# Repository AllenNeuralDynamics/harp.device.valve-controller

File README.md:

A Harp-compliant, 16-channel MOSFET Output board for valve control.

## Features
* Up to 5A total current consumption
* Up to 2A on any single output channel
* 8-GPIO expansion header

## Enclosure
See the companion [Onshape project](https://cad.onshape.com/documents/b68e9ca81d13baa37ddbb87a/w/239401edd39de6ea07d882fc/e/2e7e06ce5de5ab57a801ffd8) for the PCBA enclosure.

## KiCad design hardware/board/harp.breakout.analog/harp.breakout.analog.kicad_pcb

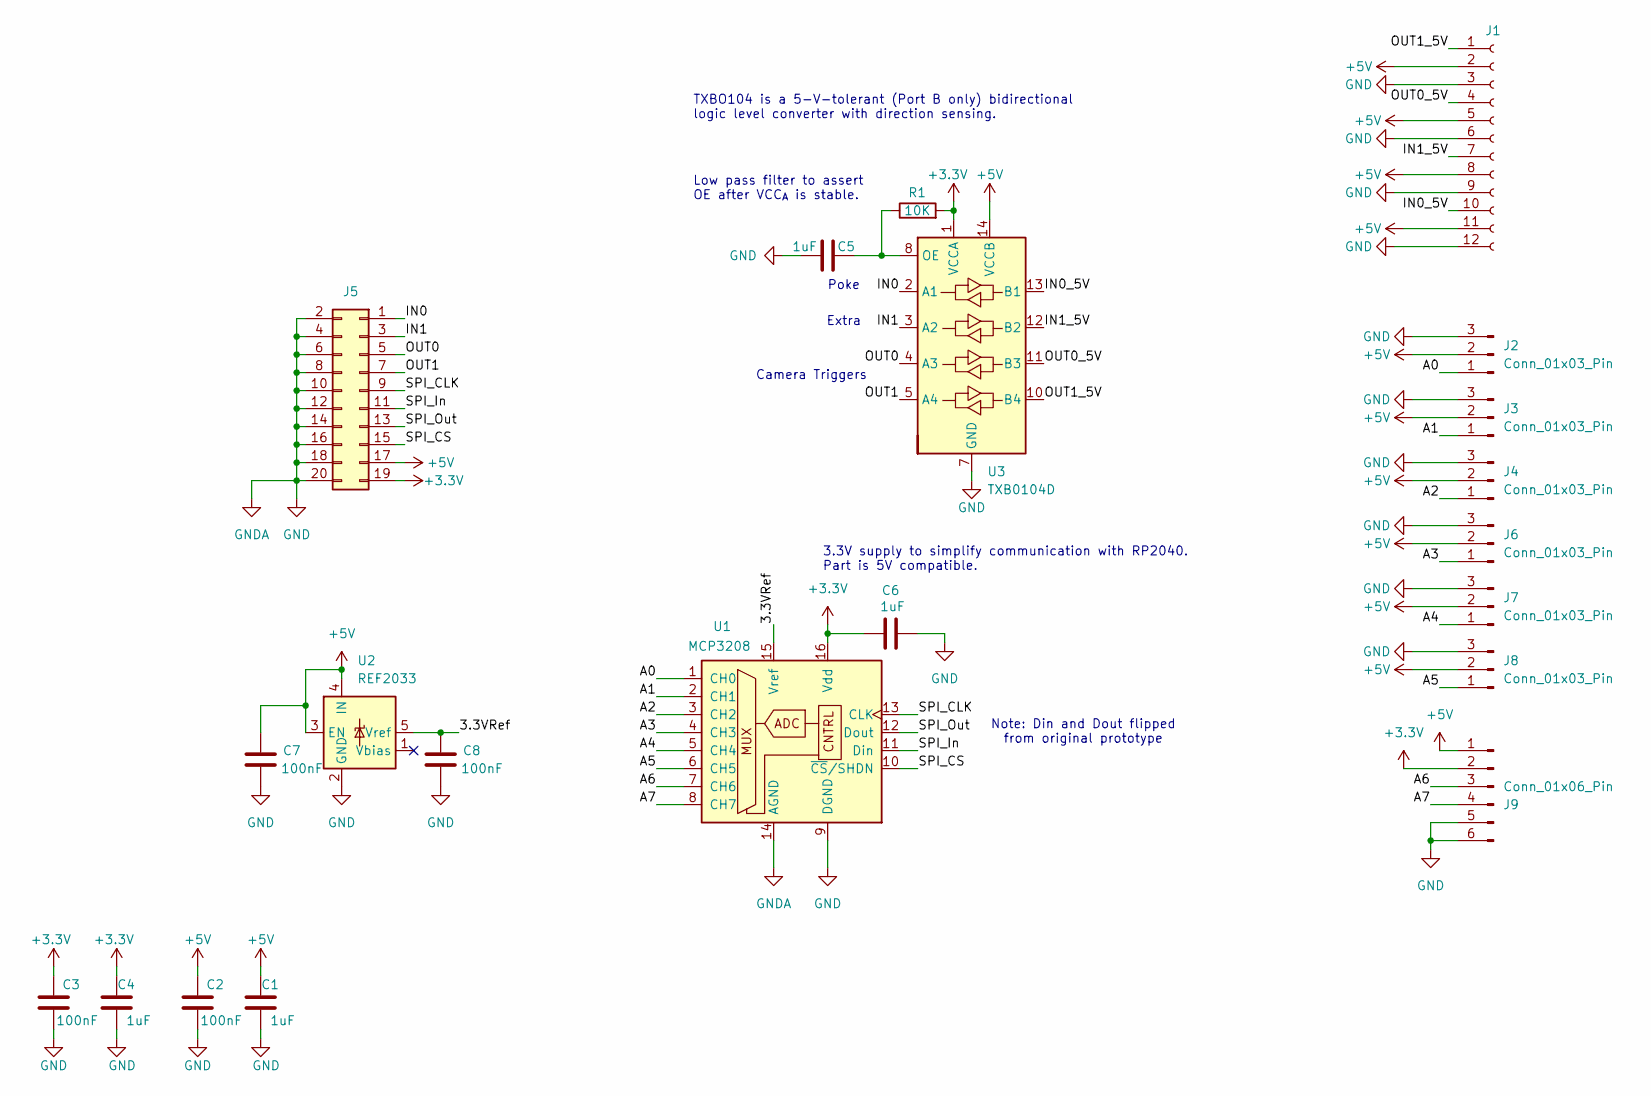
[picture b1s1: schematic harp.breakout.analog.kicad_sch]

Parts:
C1, C4, C5: 1uF; C_0402_1005Metric_Pad0.74x0.62mm_HandSolder; Rated Voltage 35V
C2, C3: 100nF; C_0402_1005Metric_Pad0.74x0.62mm_HandSolder; Rated Voltage 50V; Tolerance 10%
C6: 1uF; C_0402_1005Metric_Pad0.74x0.62mm_HandSolder
C7, C8: 100nF; C_0402_1005Metric_Pad0.74x0.62mm_HandSolder
J1: Conn_01x12_Socket; 3M_Mini-Clamp-Socket-37212-62M3-003PL-3x4_Vertical
J2, J3, J4, J6, J7, J8: Conn_01x03_Pin; CONN_705530002_03_MOL
J5: Conn_02x10_Odd_Even; PinSocket_2x10_P2.54mm_Vertical
J9: Conn_01x06_Pin; PinHeader_1x06_P2.54mm_Vertical
R1: 10K; R_0402_1005Metric_Pad0.72x0.64mm_HandSolder
U1: MCP3208; DIP-16_W7.62mm_LongPads
U2: REF2033; SOT-23-5
U3: TXB0104D; SOIC-14_3.9x8.7mm_P1.27mm

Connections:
+3.3V: C3.2, C4.1, C6.1, J5.19, J9.2, R1.2, U1.16 (Vdd), U3.1 (VCCA)
+5V: C1.1, C2.2, C7.1, J1.2, J1.5, J1.8, J1.11, J2.2, J3.2, J4.2, J5.17, J6.2, J7.2, J8.2, J9.1, U2.3 (EN), U2.4 (IN), U3.14 (VCCB)
/3.3VRef: C8.1, U1.15 (Vref), U2.5 (Vref)
/A0: J2.1, U1.1 (CH0)
/A1: J3.1, U1.2 (CH1)
/A2: J4.1, U1.3 (CH2)
/A3: J6.1, U1.4 (CH3)
/A4: J7.1, U1.5 (CH4)
/A5: J8.1, U1.6 (CH5)
/A6: J9.3, U1.7 (CH6)
/A7: J9.4, U1.8 (CH7)
/IN0: J5.1, U3.2 (A1)
/IN0_5V: J1.10, U3.13 (B1)
/IN1: J5.3, U3.3 (A2)
/IN1_5V: J1.7, U3.12 (B2)
/OUT0: J5.5, U3.4 (A3)
/OUT0_5V: J1.4, U3.11 (B3)
/OUT1: J5.7, U3.5 (A4)
/OUT1_5V: J1.1, U3.10 (B4)
/SPI_CLK: J5.9, U1.13 (CLK)
/SPI_CS: J5.15, U1.10 (~CS/SHDN)
/SPI_In: J5.11, U1.11 (Din)
/SPI_Out: J5.13, U1.12 (Dout)
GND: C1.2, C2.1, C3.1, C4.2, C5.2, C6.2, C7.2, C8.2, J1.3, J1.6, J1.9, J1.12, J2.3, J3.3, J4.3, J5.2, J5.4, J5.6, J5.8, J5.10, J5.12, J5.14, J5.16, J5.18, J5.20, J6.3, J7.3, J8.3, J9.5, J9.6, U1.9 (DGND), U1.14 (AGND), U2.2 (GND), U3.7 (GND)
unnamed: C5.1, R1.1, U3.8 (OE)

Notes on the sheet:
3.3V supply to simplify communication with RP2040. Part is 5V compatible.
Camera Triggers
Low pass filter to assert OE after VCC_{A} is stable.
Poke
TXBO104 is a 5-V-tolerant (Port B only) bidirectional logic level converter with direction sensing.
Note: Din and Dout flipped from original prototype
Extra

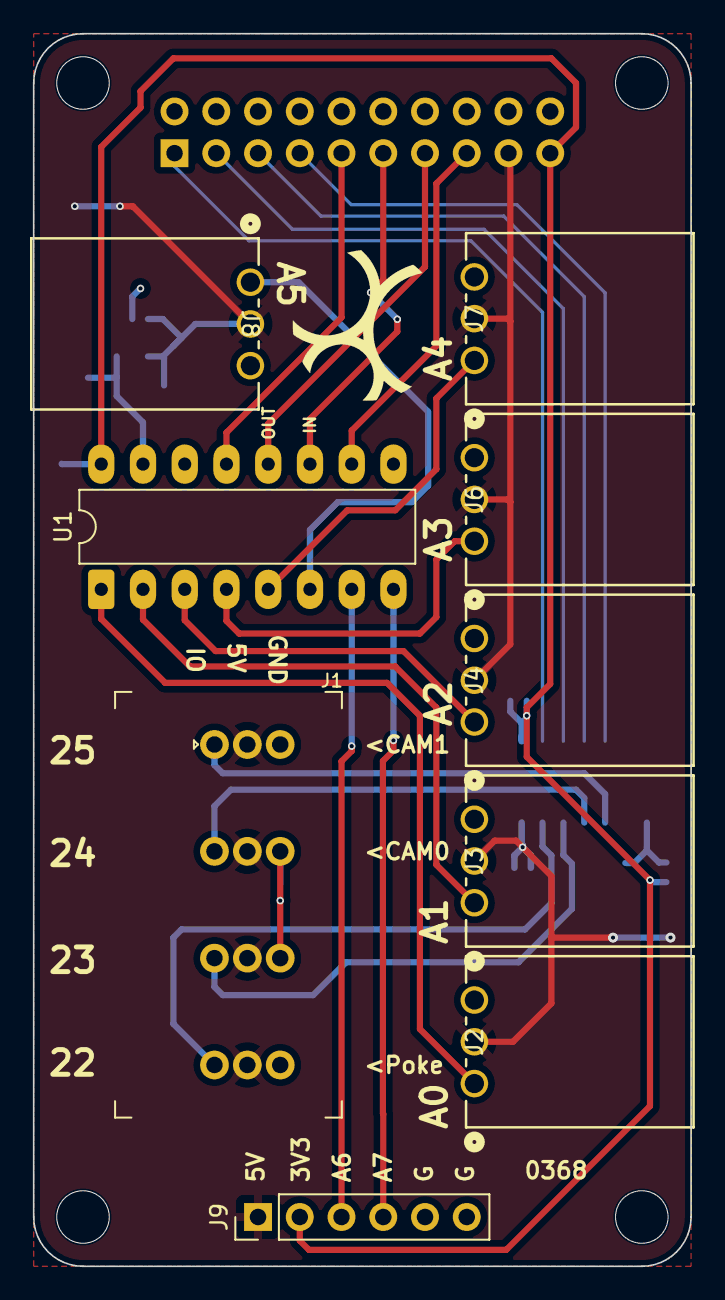
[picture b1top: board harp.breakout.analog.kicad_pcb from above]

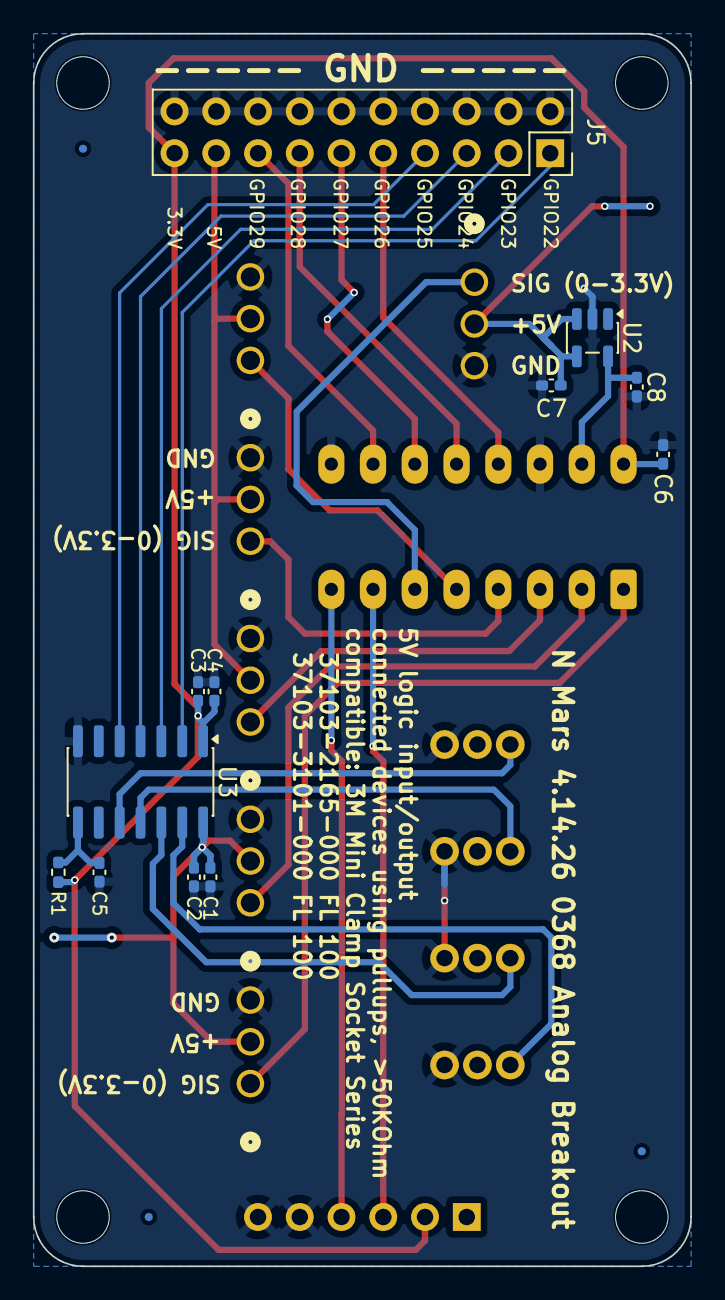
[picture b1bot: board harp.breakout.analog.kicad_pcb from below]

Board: 2 copper layers, 40.0 x 75.0 mm, 24 parts (15 on the bottom side), 25 nets.

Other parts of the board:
FID2, FID2#2, FID2#3: Fiducial; Fiducial_0.5mm_Mask1mm

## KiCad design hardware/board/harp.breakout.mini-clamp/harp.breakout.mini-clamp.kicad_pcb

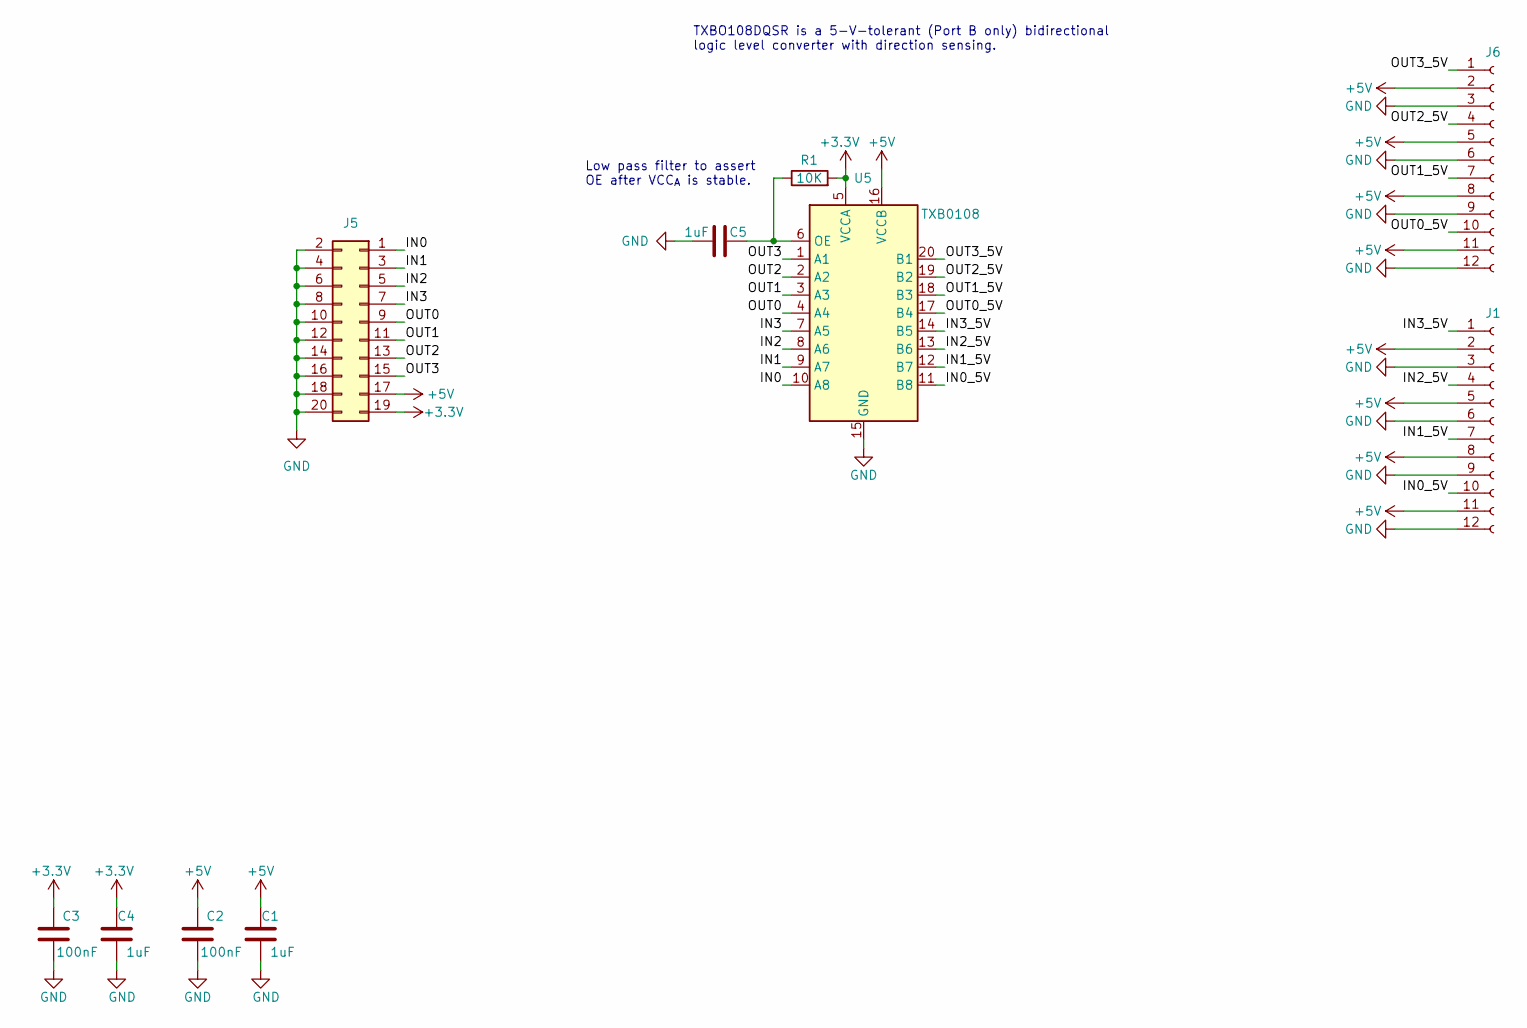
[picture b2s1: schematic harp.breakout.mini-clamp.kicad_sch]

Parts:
C1, C4, C5: 1uF; C_0402_1005Metric_Pad0.74x0.62mm_HandSolder; Rated Voltage 35V
C2, C3: 100nF; C_0402_1005Metric_Pad0.74x0.62mm_HandSolder; Rated Voltage 50V; Tolerance 10%
J1, J6: Conn_01x12_Socket; 3M_Mini-Clamp-Socket-37212-62M3-003PL-3x4_Vertical
J5: Conn_02x10_Odd_Even; PinSocket_2x10_P2.54mm_Vertical
R1: 10K; R_0402_1005Metric_Pad0.72x0.64mm_HandSolder
U5: TXB0108; TSSOP-20_4.4x6.5mm_P0.65mm

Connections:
+3.3V: C3.2, C4.1, J5.19, R1.2, U5.5 (VCCA)
+5V: C1.1, C2.2, J1.2, J1.5, J1.8, J1.11, J5.17, J6.2, J6.5, J6.8, J6.11, U5.16 (VCCB)
/IN0: J5.1, U5.10 (A8)
/IN0_5V: J1.10, U5.11 (B8)
/IN1: J5.3, U5.9 (A7)
/IN1_5V: J1.7, U5.12 (B7)
/IN2: J5.5, U5.8 (A6)
/IN2_5V: J1.4, U5.13 (B6)
/IN3: J5.7, U5.7 (A5)
/IN3_5V: J1.1, U5.14 (B5)
/OUT0: J5.9, U5.4 (A4)
/OUT0_5V: J6.10, U5.17 (B4)
/OUT1: J5.11, U5.3 (A3)
/OUT1_5V: J6.7, U5.18 (B3)
/OUT2: J5.13, U5.2 (A2)
/OUT2_5V: J6.4, U5.19 (B2)
/OUT3: J5.15, U5.1 (A1)
/OUT3_5V: J6.1, U5.20 (B1)
GND: C1.2, C2.1, C3.1, C4.2, C5.2, J1.3, J1.6, J1.9, J1.12, J5.2, J5.4, J5.6, J5.8, J5.10, J5.12, J5.14, J5.16, J5.18, J5.20, J6.3, J6.6, J6.9, J6.12, U5.15 (GND)
unnamed: C5.1, R1.1, U5.6 (OE)

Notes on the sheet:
Low pass filter to assert OE after VCC_{A} is stable.
TXBO108DQSR is a 5-V-tolerant (Port B only) bidirectional logic level converter with direction sensing.

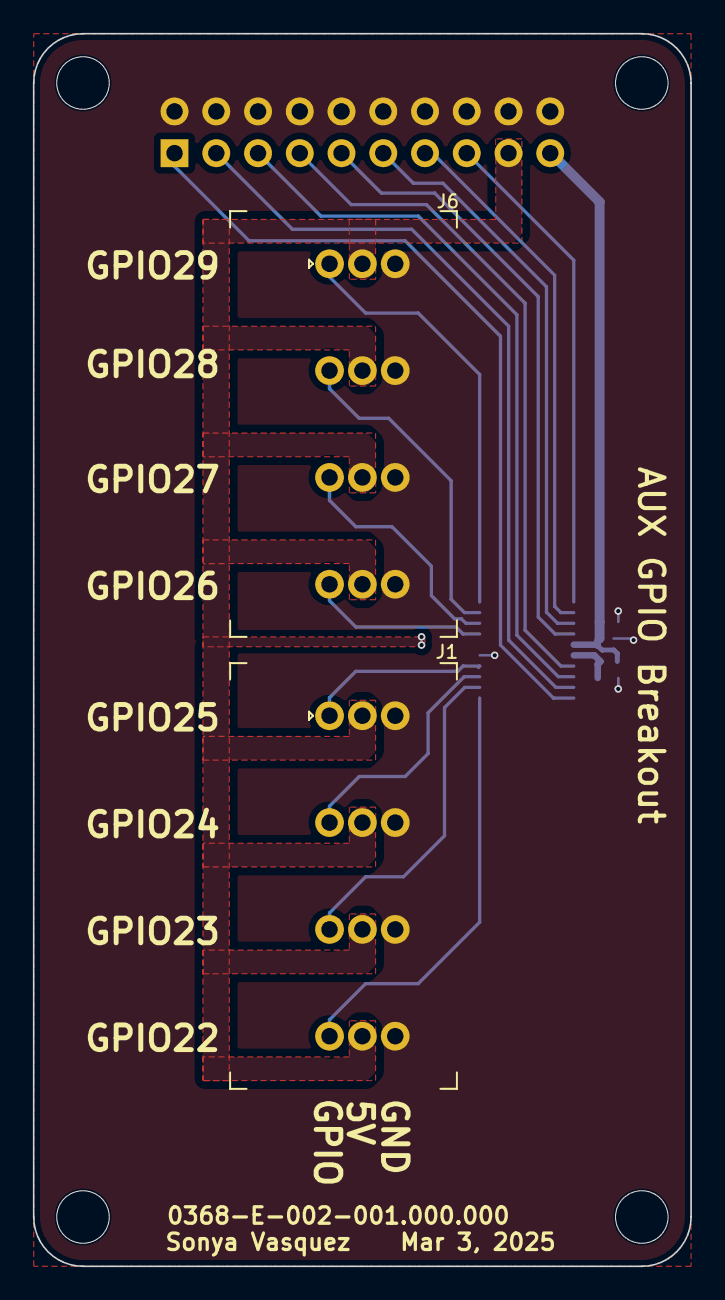
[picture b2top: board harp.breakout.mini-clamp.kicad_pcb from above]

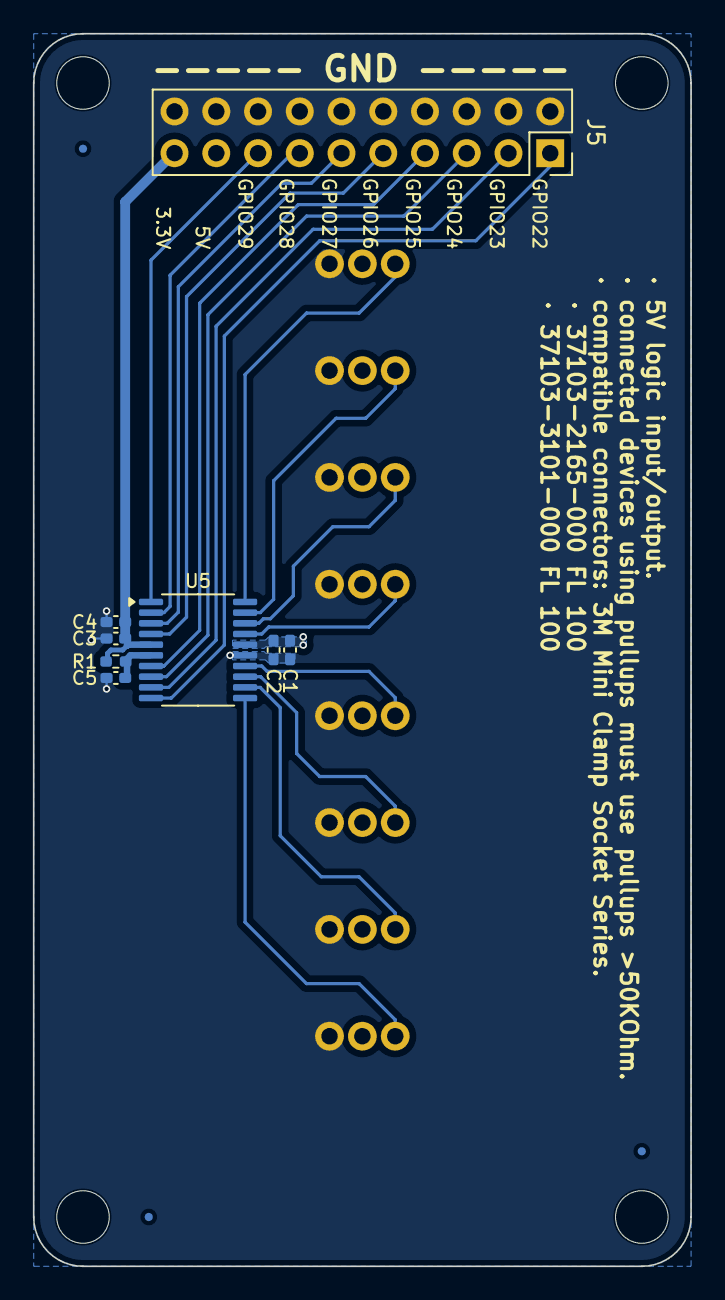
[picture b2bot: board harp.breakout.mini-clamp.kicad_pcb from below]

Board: 2 copper layers, 40.0 x 75.0 mm, 13 parts (11 on the bottom side), 20 nets.

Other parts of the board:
FID2, FID2#2, FID2#3: Fiducial; Fiducial_0.5mm_Mask1mm

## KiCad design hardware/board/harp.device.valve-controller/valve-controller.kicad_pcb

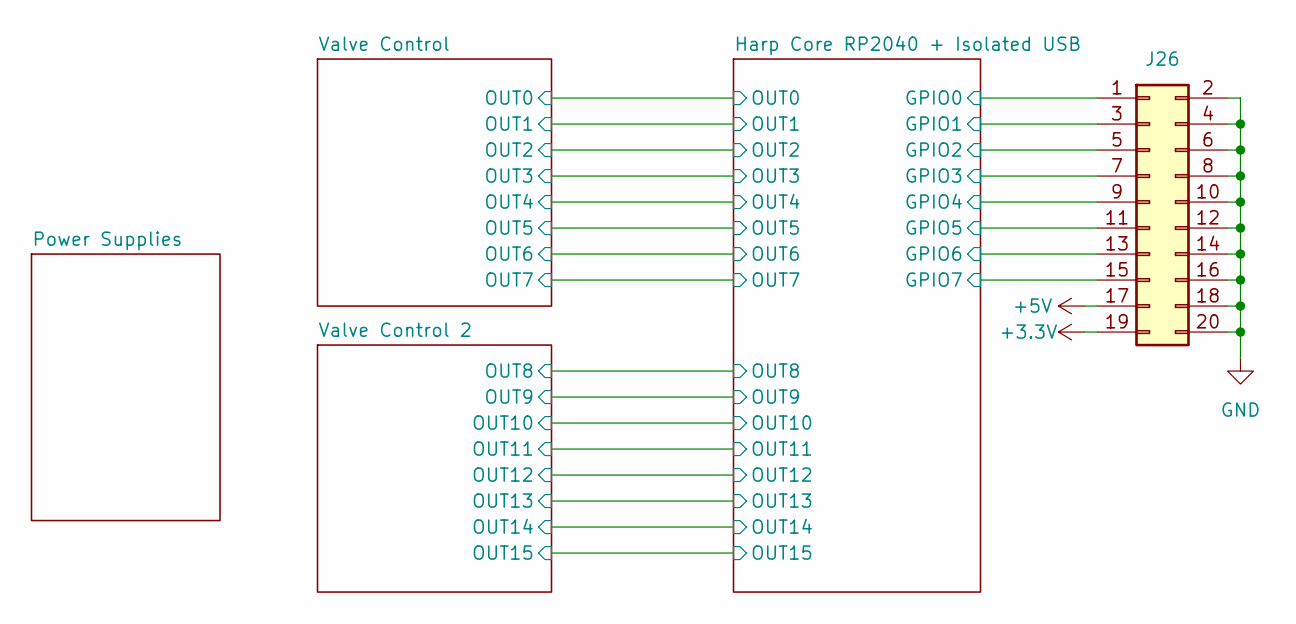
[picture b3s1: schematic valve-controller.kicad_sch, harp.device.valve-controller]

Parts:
J26: Conn_02x10_Odd_Even; PinHeader_2x10_P2.54mm_Vertical_SMD

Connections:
+3.3V: J26.19; also elsewhere on the board
+5V: J26.17; also elsewhere on the board
/Harp Core RP2040 + Isolated USB/GPIO0: J26.1; also elsewhere on the board
/Harp Core RP2040 + Isolated USB/GPIO1: J26.3; also elsewhere on the board
/Harp Core RP2040 + Isolated USB/GPIO2: J26.5; also elsewhere on the board
/Harp Core RP2040 + Isolated USB/GPIO3: J26.7; also elsewhere on the board
/Harp Core RP2040 + Isolated USB/GPIO4: J26.9; also elsewhere on the board
/Harp Core RP2040 + Isolated USB/GPIO5: J26.11; also elsewhere on the board
/Harp Core RP2040 + Isolated USB/GPIO6: J26.13; also elsewhere on the board
/Harp Core RP2040 + Isolated USB/GPIO7: J26.15; also elsewhere on the board
GND: J26.2, J26.4, J26.6, J26.8, J26.10, J26.12, J26.14, J26.16, J26.18, J26.20; also elsewhere on the board

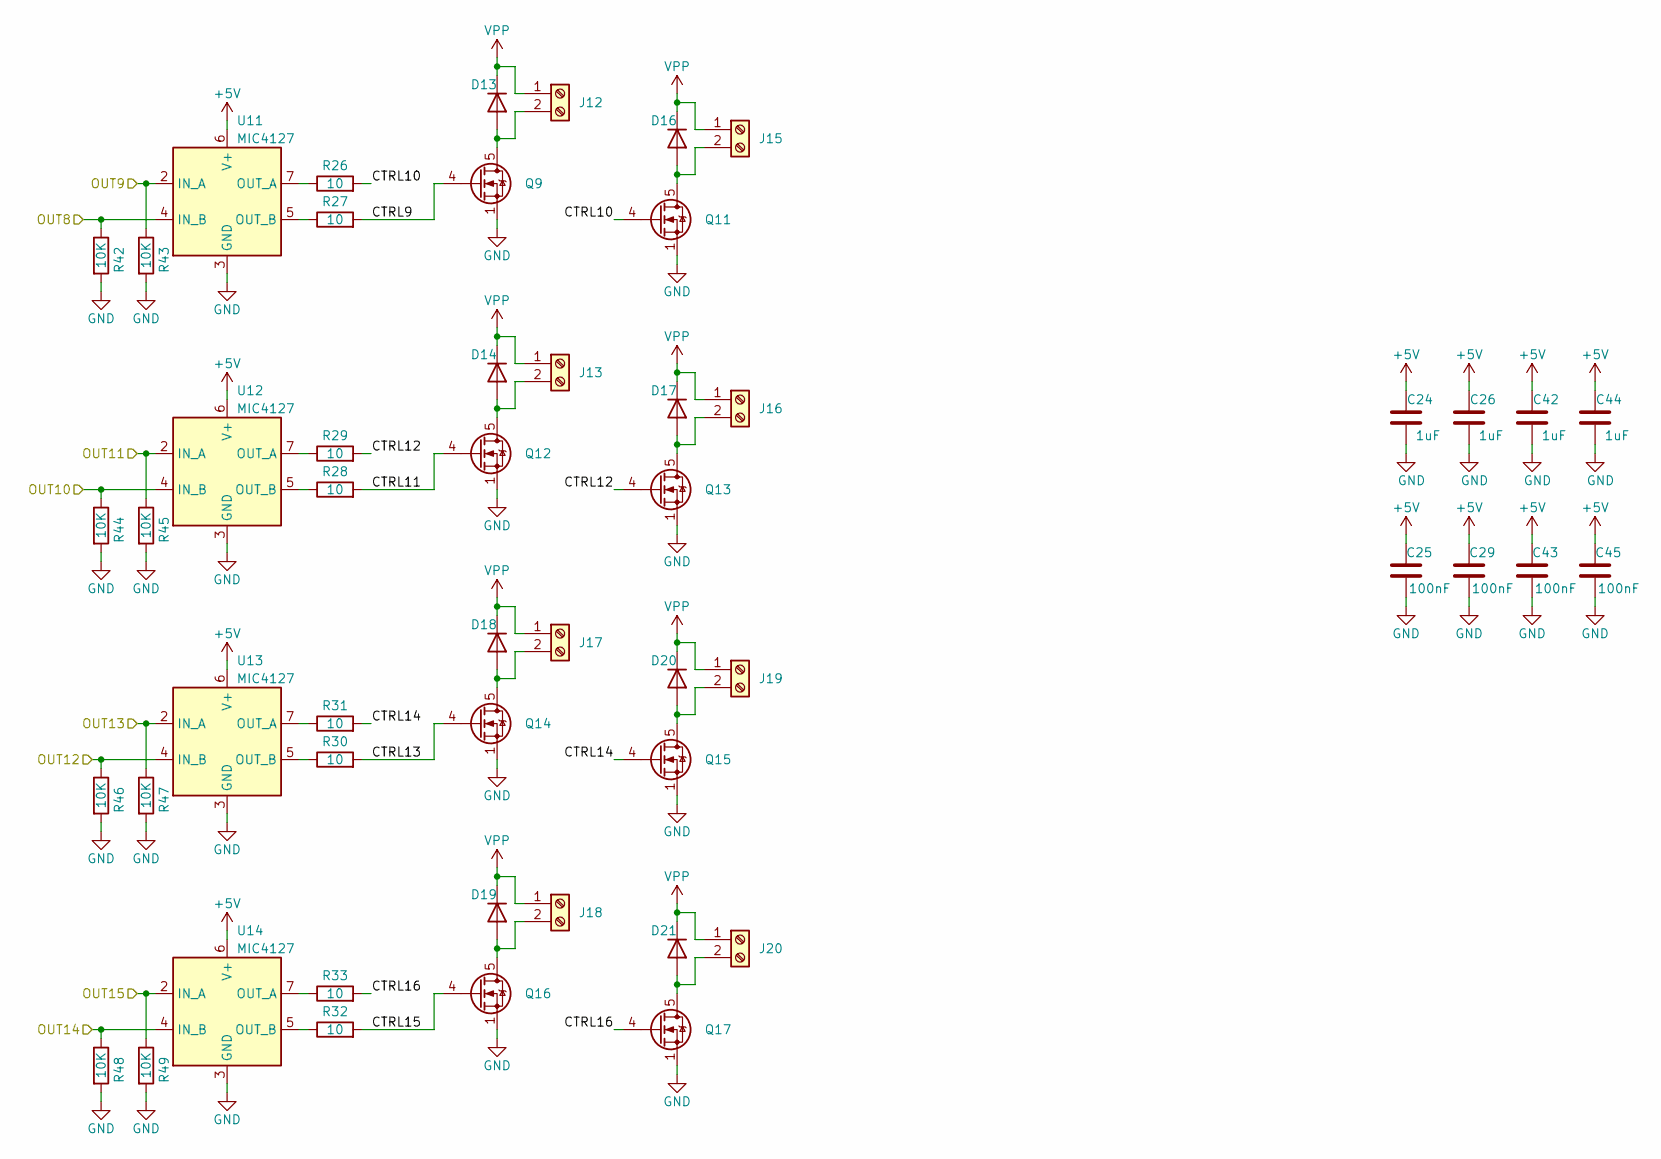
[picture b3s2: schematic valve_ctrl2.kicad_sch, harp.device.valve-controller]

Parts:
C24, C26, C42, C44: 1uF; C_0402_1005Metric; Rated Voltage 35V
C25, C29, C43, C45: 100nF; C_0402_1005Metric; Rated Voltage 50V; Tolerance 10%
D13, D14, D16, D17, D18, D19, D20, D21: 1N4007FL; D_SOD-123F
J12, J13, J15, J16, J17, J18, J19, J20: Screw_Terminal_01x02; PhoenixContact_MC_1,5_2-G-3.5_1x02_P3.50mm_Horizontal
Q9, Q11, Q12, Q13, Q14, Q15, Q16, Q17: CSD17570Q5B; TDSON-8-1
R26, R27, R28, R29, R30, R31, R32, R33: 10; R_0603_1608Metric; Tolerance 1%
R42, R43, R44, R45, R46, R47, R48, R49: 10K; R_0402_1005Metric
U11, U12, U13, U14: MIC4127; MSOP-8-1EP_3x3mm_P0.65mm_EP1.5x1.8mm

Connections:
+5V: C24.1, C25.2, C26.1, C29.2, C42.1, C43.2, C44.1, C45.2, U11.6 (V+), U12.6 (V+), U13.6 (V+), U14.6 (V+); also elsewhere on the board
/Harp Core RP2040 + Isolated USB/OUT8: R42.1, U11.4 (IN_B); also elsewhere on the board
/Harp Core RP2040 + Isolated USB/OUT9: R43.1, U11.2 (IN_A); also elsewhere on the board
/Harp Core RP2040 + Isolated USB/OUT10: R44.1, U12.4 (IN_B); also elsewhere on the board
/Harp Core RP2040 + Isolated USB/OUT11: R45.1, U12.2 (IN_A); also elsewhere on the board
/Harp Core RP2040 + Isolated USB/OUT12: R46.1, U13.4 (IN_B); also elsewhere on the board
/Harp Core RP2040 + Isolated USB/OUT13: R47.1, U13.2 (IN_A); also elsewhere on the board
/Harp Core RP2040 + Isolated USB/OUT14: R48.1, U14.4 (IN_B); also elsewhere on the board
/Harp Core RP2040 + Isolated USB/OUT15: R49.1, U14.2 (IN_A); also elsewhere on the board
/Valve Control 2/CTRL9: Q9.4 (G), R27.2
/Valve Control 2/CTRL10: Q11.4 (G), R26.2
/Valve Control 2/CTRL11: Q12.4 (G), R28.2
/Valve Control 2/CTRL12: Q13.4 (G), R29.2
/Valve Control 2/CTRL13: Q14.4 (G), R30.2
/Valve Control 2/CTRL14: Q15.4 (G), R31.2
/Valve Control 2/CTRL15: Q16.4 (G), R32.2
/Valve Control 2/CTRL16: Q17.4 (G), R33.2
GND: C24.2, C25.1, C26.2, C29.1, C42.2, C43.1, C44.2, C45.1, Q9.1 (S), Q9.2 (S), Q9.3 (S), Q11.1 (S), Q11.2 (S), Q11.3 (S), Q12.1 (S), Q12.2 (S), Q12.3 (S), Q13.1 (S), Q13.2 (S), Q13.3 (S), Q14.1 (S), Q14.2 (S), Q14.3 (S), Q15.1 (S), Q15.2 (S), Q15.3 (S), Q16.1 (S), Q16.2 (S), Q16.3 (S), Q17.1 (S), Q17.2 (S), Q17.3 (S), R42.2, R43.2, R44.2, R45.2, R46.2, R47.2, R48.2, R49.2, U11.3 (GND), U11.9 (GND), U12.3 (GND), U12.9 (GND), U13.3 (GND), U13.9 (GND), U14.3 (GND), U14.9 (GND); also elsewhere on the board
unnamed: D13.2 (A), J12.2, Q9.5 (D)
unnamed: D14.2 (A), J13.2, Q12.5 (D)
unnamed: D16.2 (A), J15.2, Q11.5 (D)
unnamed: D17.2 (A), J16.2, Q13.5 (D)
unnamed: D18.2 (A), J17.2, Q14.5 (D)
unnamed: D19.2 (A), J18.2, Q16.5 (D)
unnamed: D20.2 (A), J19.2, Q15.5 (D)
unnamed: D21.2 (A), J20.2, Q17.5 (D)
unnamed: R26.1, U11.7 (OUT_A)
unnamed: R27.1, U11.5 (OUT_B)
unnamed: R29.1, U12.7 (OUT_A)
unnamed: R28.1, U12.5 (OUT_B)
unnamed: R31.1, U13.7 (OUT_A)
unnamed: R30.1, U13.5 (OUT_B)
unnamed: R33.1, U14.7 (OUT_A)
unnamed: R32.1, U14.5 (OUT_B)
VPP: D13.1 (K), D14.1 (K), D16.1 (K), D17.1 (K), D18.1 (K), D19.1 (K), D20.1 (K), D21.1 (K), J12.1, J13.1, J15.1, J16.1, J17.1, J18.1, J19.1, J20.1; also elsewhere on the board

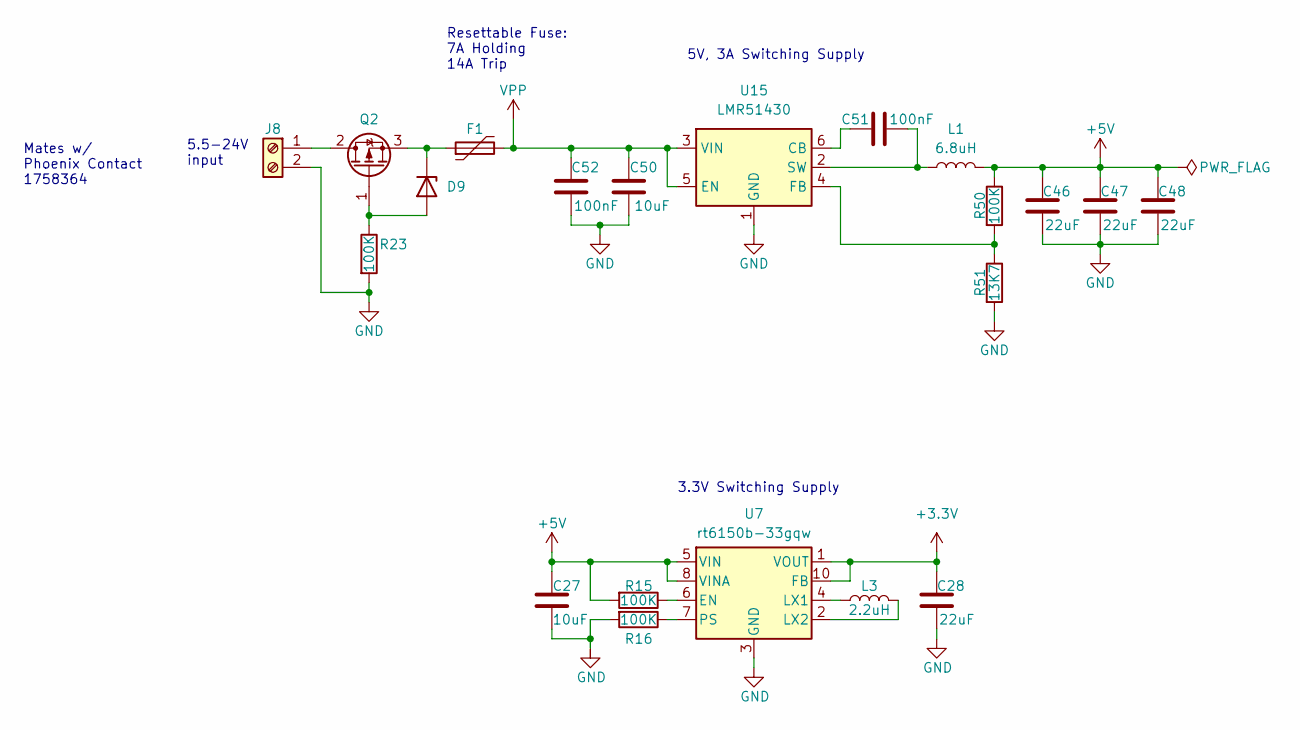
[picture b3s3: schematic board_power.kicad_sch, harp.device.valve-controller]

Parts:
C27, C50: 10uF; C_0805_2012Metric
C28, C46, C47, C48: 22uF; C_0805_2012Metric; Rated Voltage 10V
C51, C52: 100nF; C_0402_1005Metric; Rated Voltage 50V; Tolerance 10%
D9: BZV55B15; D_MiniMELF
F1: Polyfuse; Fuse_2920_7451Metric
J8: Screw_Terminal_01x02; PhoenixContact_MSTBA_2,5_2-G-5,08_1x02_P5.08mm_Horizontal
L1: 6.8uH; L_Bourns_SRR1260
L3: 2.2uH; L_0603_1608Metric
Q2: GSFD4005; TO-252-2
R15, R16, R23, R50: 100K; R_0402_1005Metric; Tolerance 1%
R51: 13K7; R_0402_1005Metric; Tolerance 1%
U7: rt6150b-33gqw; WDFN-10-1EP_2.5x2.5mm_P0.5_EP1.25x2.1mm
U15: LMR51430; SOT-23-6

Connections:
+3.3V: C28.2, U7.1 (VOUT), U7.10 (FB); also elsewhere on the board
+5V: C27.1, C46.2, C47.2, C48.2, L1.2, R15.2, R50.1, U7.5 (VIN), U7.8 (VINA); also elsewhere on the board
GND: C27.2, C28.1, C46.1, C47.1, C48.1, C50.2, C52.1, J8.2, R16.2, R23.2, R51.2, U7.3 (GND), U7.9 (GND), U7.11 (GND), U15.1 (GND); also elsewhere on the board
unnamed: D9.2 (A), Q2.1 (G), R23.1
unnamed: D9.1 (K), F1.1, Q2.3 (S)
unnamed: J8.1, Q2.2 (D)
unnamed: R15.1, U7.6 (EN)
unnamed: L3.1, U7.4 (LX1)
unnamed: L3.2, U7.2 (LX2)
unnamed: R16.1, U7.7 (PS)
unnamed: C51.2, U15.6 (CB)
unnamed: R50.2, R51.1, U15.4 (FB)
unnamed: C51.1, L1.1, U15.2 (SW)
VPP: C50.1, C52.2, F1.2, U15.3 (VIN), U15.5 (EN); also elsewhere on the board

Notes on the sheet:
5.5-24V input
3.3V Switching Supply
Mates w/ Phoenix Contact 1758364
5V, 3A Switching Supply
Resettable Fuse: 7A Holding 14A Trip

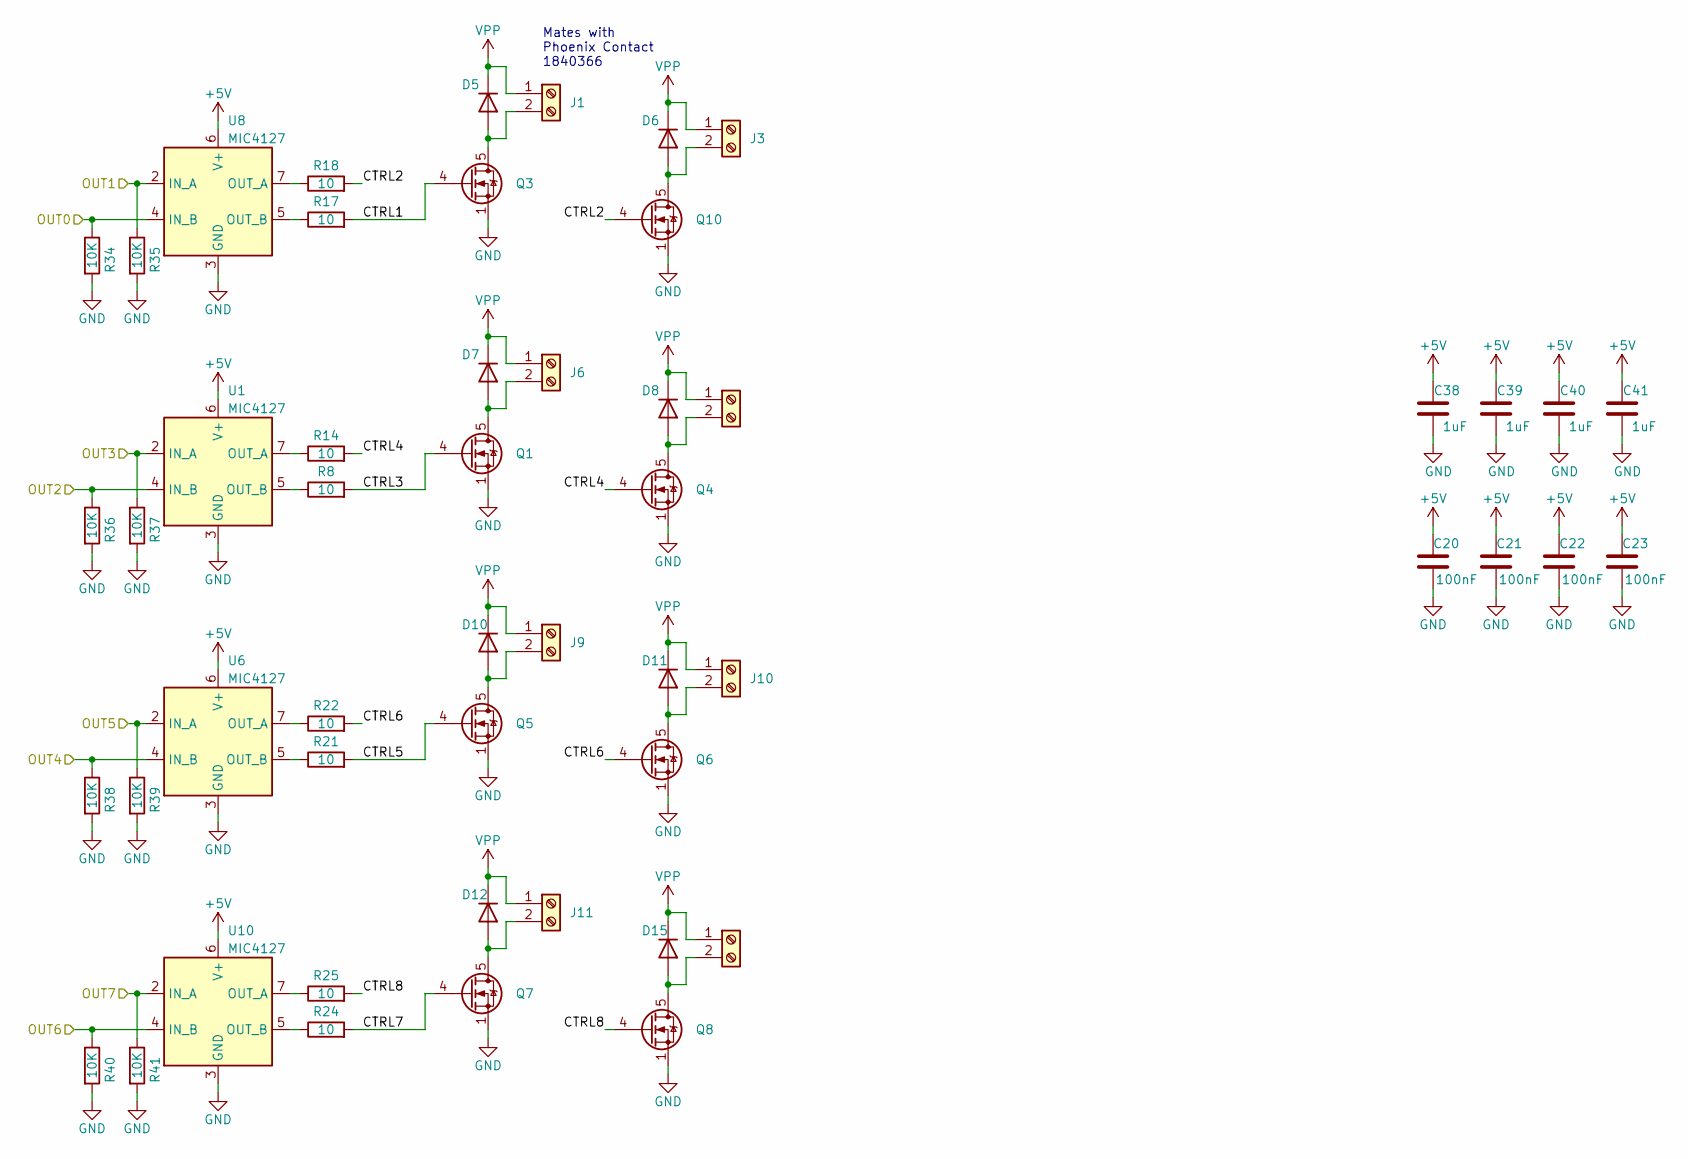
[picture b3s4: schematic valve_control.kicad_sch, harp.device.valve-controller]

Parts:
C20, C21, C22, C23: 100nF; C_0402_1005Metric; Rated Voltage 50V; Tolerance 10%
C38, C39, C40, C41: 1uF; C_0402_1005Metric; Rated Voltage 35V
D5, D6, D7, D8, D10, D11, D12, D15: 1N4007FL; D_SOD-123F
J1, J3, J6, J7, J9, J10, J11, J14: Screw_Terminal_01x02; PhoenixContact_MC_1,5_2-G-3.5_1x02_P3.50mm_Horizontal
Q1, Q3, Q4, Q5, Q6, Q7, Q8, Q10: CSD17570Q5B; TDSON-8-1
R8, R14, R17, R18, R21, R22, R24, R25: 10; R_0603_1608Metric; Tolerance 1%
R34, R35, R36, R37, R38, R39, R40, R41: 10K; R_0402_1005Metric
U1, U6, U8, U10: MIC4127; MSOP-8-1EP_3x3mm_P0.65mm_EP1.5x1.8mm

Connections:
+5V: C20.2, C21.2, C22.2, C23.2, C38.1, C39.1, C40.1, C41.1, U1.6 (V+), U6.6 (V+), U8.6 (V+), U10.6 (V+); also elsewhere on the board
/Harp Core RP2040 + Isolated USB/OUT0: R34.1, U8.4 (IN_B); also elsewhere on the board
/Harp Core RP2040 + Isolated USB/OUT1: R35.1, U8.2 (IN_A); also elsewhere on the board
/Harp Core RP2040 + Isolated USB/OUT2: R36.1, U1.4 (IN_B); also elsewhere on the board
/Harp Core RP2040 + Isolated USB/OUT3: R37.1, U1.2 (IN_A); also elsewhere on the board
/Harp Core RP2040 + Isolated USB/OUT4: R38.1, U6.4 (IN_B); also elsewhere on the board
/Harp Core RP2040 + Isolated USB/OUT5: R39.1, U6.2 (IN_A); also elsewhere on the board
/Harp Core RP2040 + Isolated USB/OUT6: R40.1, U10.4 (IN_B); also elsewhere on the board
/Harp Core RP2040 + Isolated USB/OUT7: R41.1, U10.2 (IN_A); also elsewhere on the board
/Valve Control/CTRL1: Q3.4 (G), R17.2
/Valve Control/CTRL2: Q10.4 (G), R18.2
/Valve Control/CTRL3: Q1.4 (G), R8.2
/Valve Control/CTRL4: Q4.4 (G), R14.2
/Valve Control/CTRL5: Q5.4 (G), R21.2
/Valve Control/CTRL6: Q6.4 (G), R22.2
/Valve Control/CTRL7: Q7.4 (G), R24.2
/Valve Control/CTRL8: Q8.4 (G), R25.2
GND: C20.1, C21.1, C22.1, C23.1, C38.2, C39.2, C40.2, C41.2, Q1.1 (S), Q1.2 (S), Q1.3 (S), Q3.1 (S), Q3.2 (S), Q3.3 (S), Q4.1 (S), Q4.2 (S), Q4.3 (S), Q5.1 (S), Q5.2 (S), Q5.3 (S), Q6.1 (S), Q6.2 (S), Q6.3 (S), Q7.1 (S), Q7.2 (S), Q7.3 (S), Q8.1 (S), Q8.2 (S), Q8.3 (S), Q10.1 (S), Q10.2 (S), Q10.3 (S), R34.2, R35.2, R36.2, R37.2, R38.2, R39.2, R40.2, R41.2, U1.3 (GND), U1.9 (GND), U6.3 (GND), U6.9 (GND), U8.3 (GND), U8.9 (GND), U10.3 (GND), U10.9 (GND); also elsewhere on the board
unnamed: D5.2 (A), J1.2, Q3.5 (D)
unnamed: D6.2 (A), J3.2, Q10.5 (D)
unnamed: D7.2 (A), J6.2, Q1.5 (D)
unnamed: D8.2 (A), J7.2, Q4.5 (D)
unnamed: D10.2 (A), J9.2, Q5.5 (D)
unnamed: D11.2 (A), J10.2, Q6.5 (D)
unnamed: D12.2 (A), J11.2, Q7.5 (D)
unnamed: D15.2 (A), J14.2, Q8.5 (D)
unnamed: R14.1, U1.7 (OUT_A)
unnamed: R8.1, U1.5 (OUT_B)
unnamed: R22.1, U6.7 (OUT_A)
unnamed: R21.1, U6.5 (OUT_B)
unnamed: R18.1, U8.7 (OUT_A)
unnamed: R17.1, U8.5 (OUT_B)
unnamed: R25.1, U10.7 (OUT_A)
unnamed: R24.1, U10.5 (OUT_B)
VPP: D5.1 (K), D6.1 (K), D7.1 (K), D8.1 (K), D10.1 (K), D11.1 (K), D12.1 (K), D15.1 (K), J1.1, J3.1, J6.1, J7.1, J9.1, J10.1, J11.1, J14.1; also elsewhere on the board

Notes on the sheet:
Mates with Phoenix Contact 1840366
